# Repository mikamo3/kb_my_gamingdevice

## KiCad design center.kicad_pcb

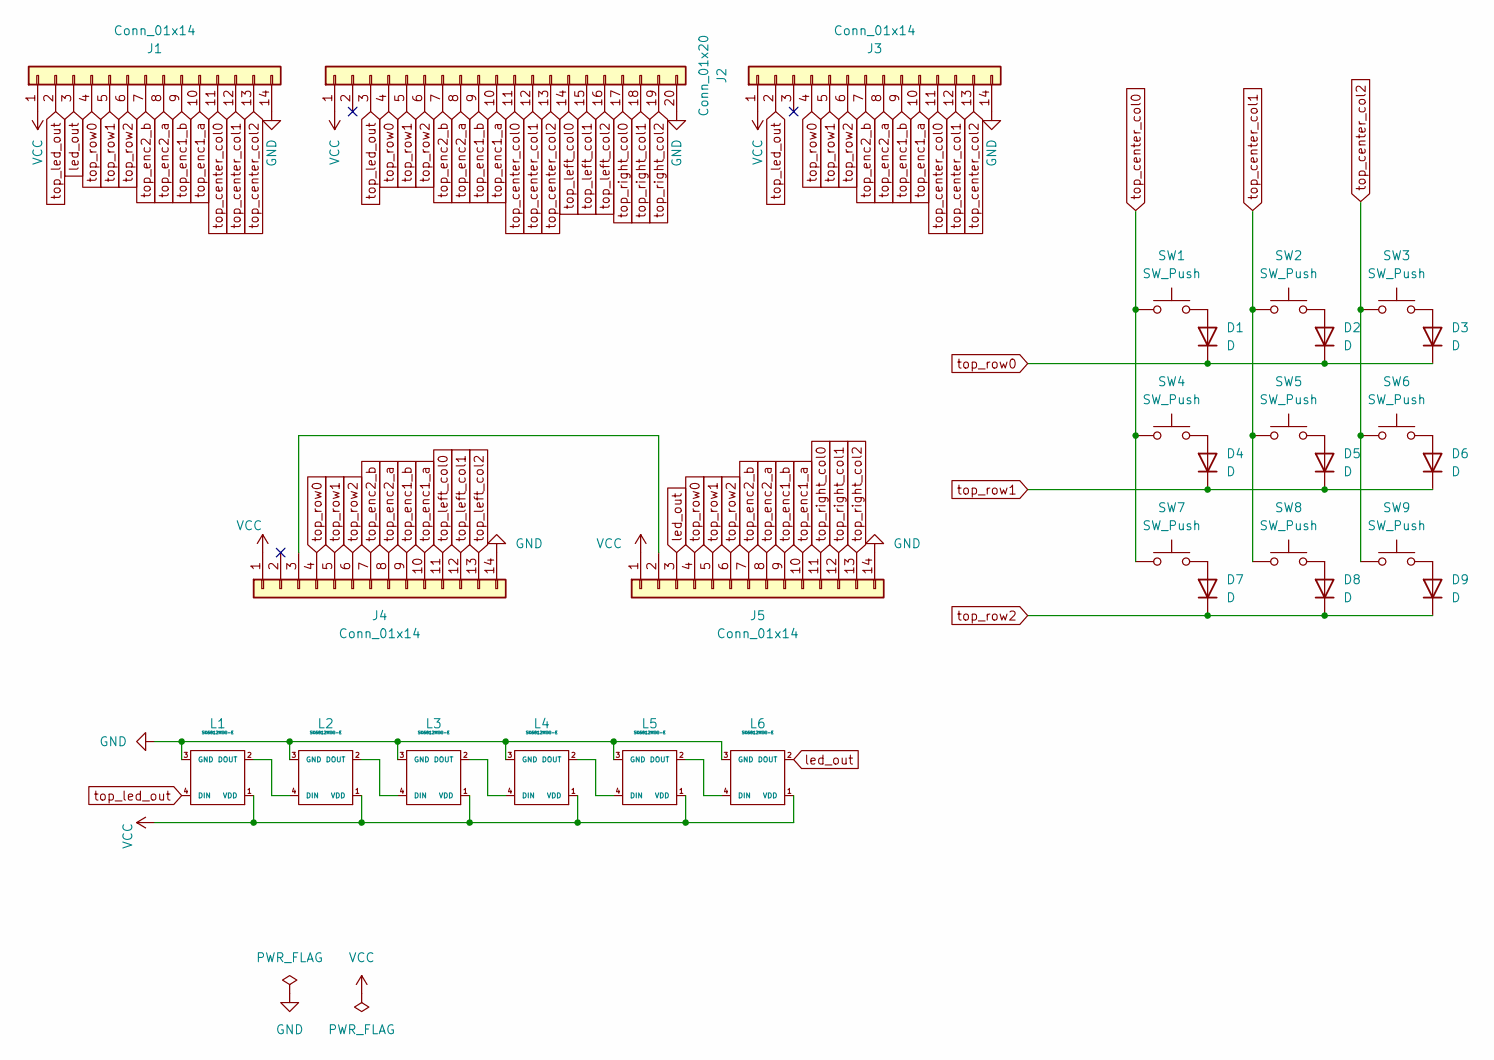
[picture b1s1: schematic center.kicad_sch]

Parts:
D1, D2, D3, D4, D5, D6, D7, D8, D9: D; D_SOD-123
J1, J3: Conn_01x14; PinSocket_2x07_P2.54mm_Horizontal
J2: Conn_01x20; PinSocket_2x10_P2.54mm_Horizontal
J4, J5: Conn_01x14; PinHeader_2x07_P2.54mm_Horizontal
L1, L2, L3, L4, L5, L6: SK6812MINI-E; YS-SK6812MINI-E
SW1, SW2, SW3, SW4, SW5, SW6, SW7, SW8, SW9: SW_Push; CherryMX_Hotswap_1u

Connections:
GND: J1.14, J2.20, J3.14, J4.14, J5.14, L1.3 (GND), L2.3 (GND), L3.3 (GND), L4.3 (GND), L5.3 (GND), L6.3 (GND)
unnamed: D1.2 (A), SW1.2
unnamed: D2.2 (A), SW2.2
unnamed: D3.2 (A), SW3.2
unnamed: D4.2 (A), SW4.2
unnamed: D5.2 (A), SW5.2
unnamed: D6.2 (A), SW6.2
unnamed: D7.2 (A), SW7.2
unnamed: D8.2 (A), SW8.2
unnamed: D9.2 (A), SW9.2
unnamed: J4.3, J5.2
unnamed: L1.2 (DOUT), L2.4 (DIN)
unnamed: L2.2 (DOUT), L3.4 (DIN)
unnamed: L3.2 (DOUT), L4.4 (DIN)
unnamed: L4.2 (DOUT), L5.4 (DIN)
unnamed: L5.2 (DOUT), L6.4 (DIN)
VCC: J1.1, J2.1, J3.1, J4.1, J5.1, L1.1 (VDD), L2.1 (VDD), L3.1 (VDD), L4.1 (VDD), L5.1 (VDD), L6.1 (VDD)
led_out: J1.3, J5.3, L6.2 (DOUT)
top_center_col0: J1.11, J2.11, J3.11, SW1.1, SW4.1, SW7.1
top_center_col1: J1.12, J2.12, J3.12, SW2.1, SW5.1, SW8.1
top_center_col2: J1.13, J2.13, J3.13, SW3.1, SW6.1, SW9.1
top_enc1_a: J1.10, J2.10, J3.10, J4.10, J5.10
top_enc1_b: J1.9, J2.9, J3.9, J4.9, J5.9
top_enc2_a: J1.8, J2.8, J3.8, J4.8, J5.8
top_enc2_b: J1.7, J2.7, J3.7, J4.7, J5.7
top_led_out: J1.2, J2.3, J3.2, L1.4 (DIN)
top_left_col0: J2.14, J4.11
top_left_col1: J2.15, J4.12
top_left_col2: J2.16, J4.13
top_right_col0: J2.17, J5.11
top_right_col1: J2.18, J5.12
top_right_col2: J2.19, J5.13
top_row0: D1.1 (K), D2.1 (K), D3.1 (K), J1.4, J2.4, J3.4, J4.4, J5.4
top_row1: D4.1 (K), D5.1 (K), D6.1 (K), J1.5, J2.5, J3.5, J4.5, J5.5
top_row2: D7.1 (K), D8.1 (K), D9.1 (K), J1.6, J2.6, J3.6, J4.6, J5.6

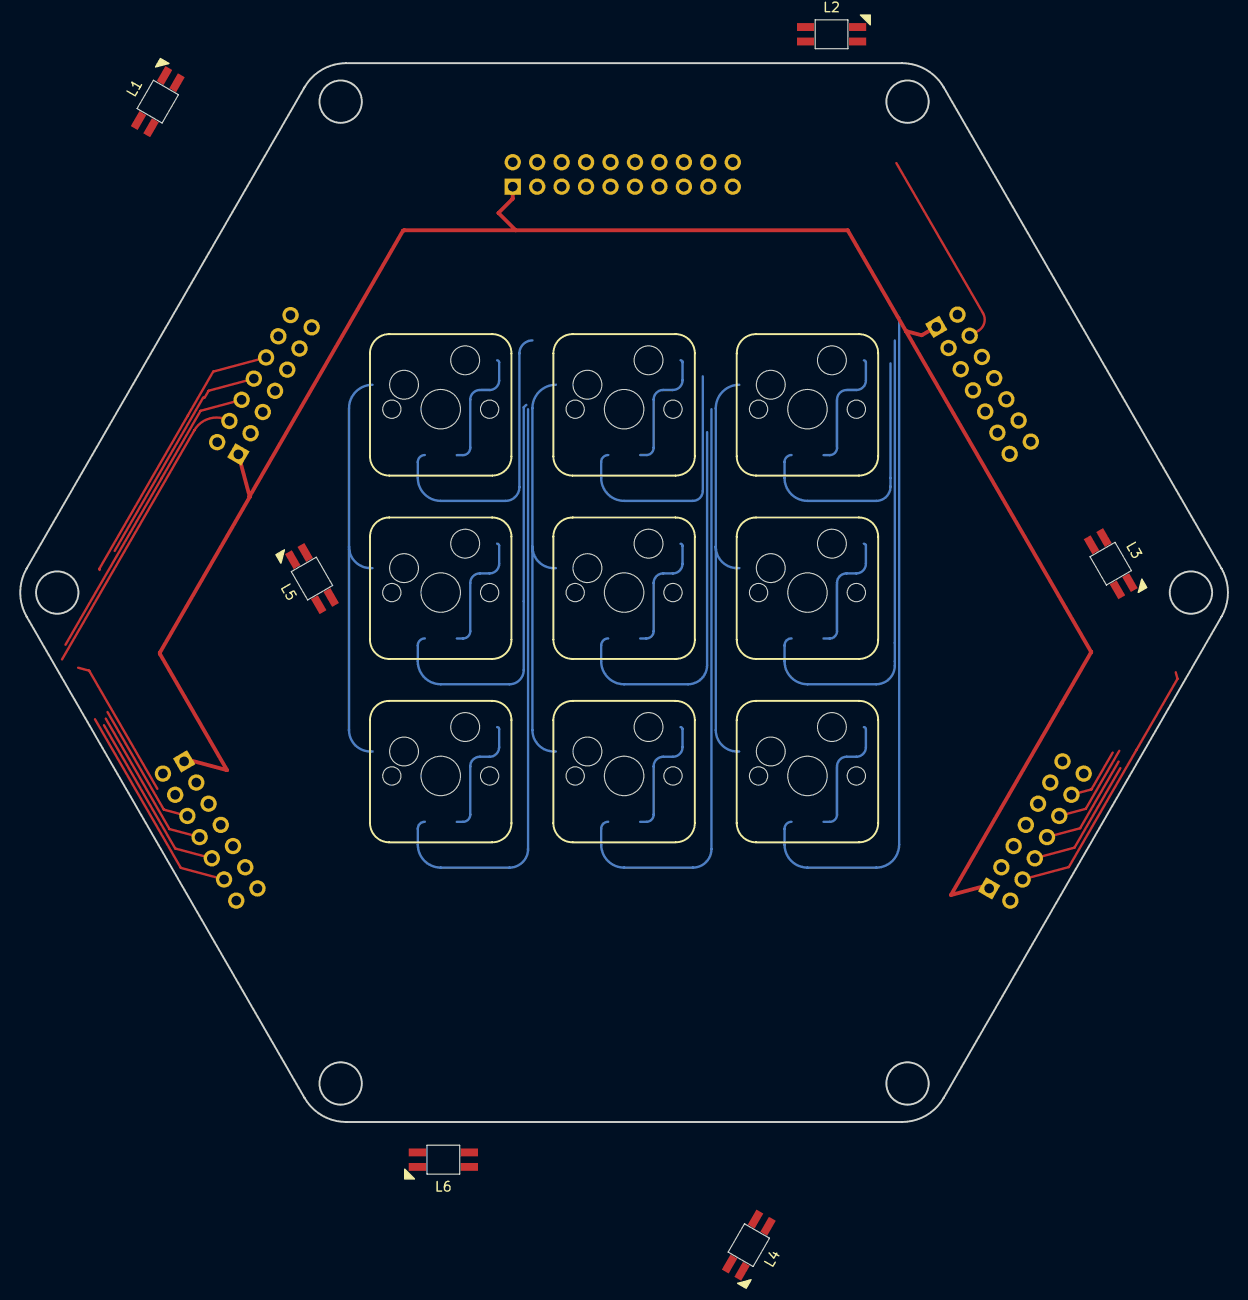
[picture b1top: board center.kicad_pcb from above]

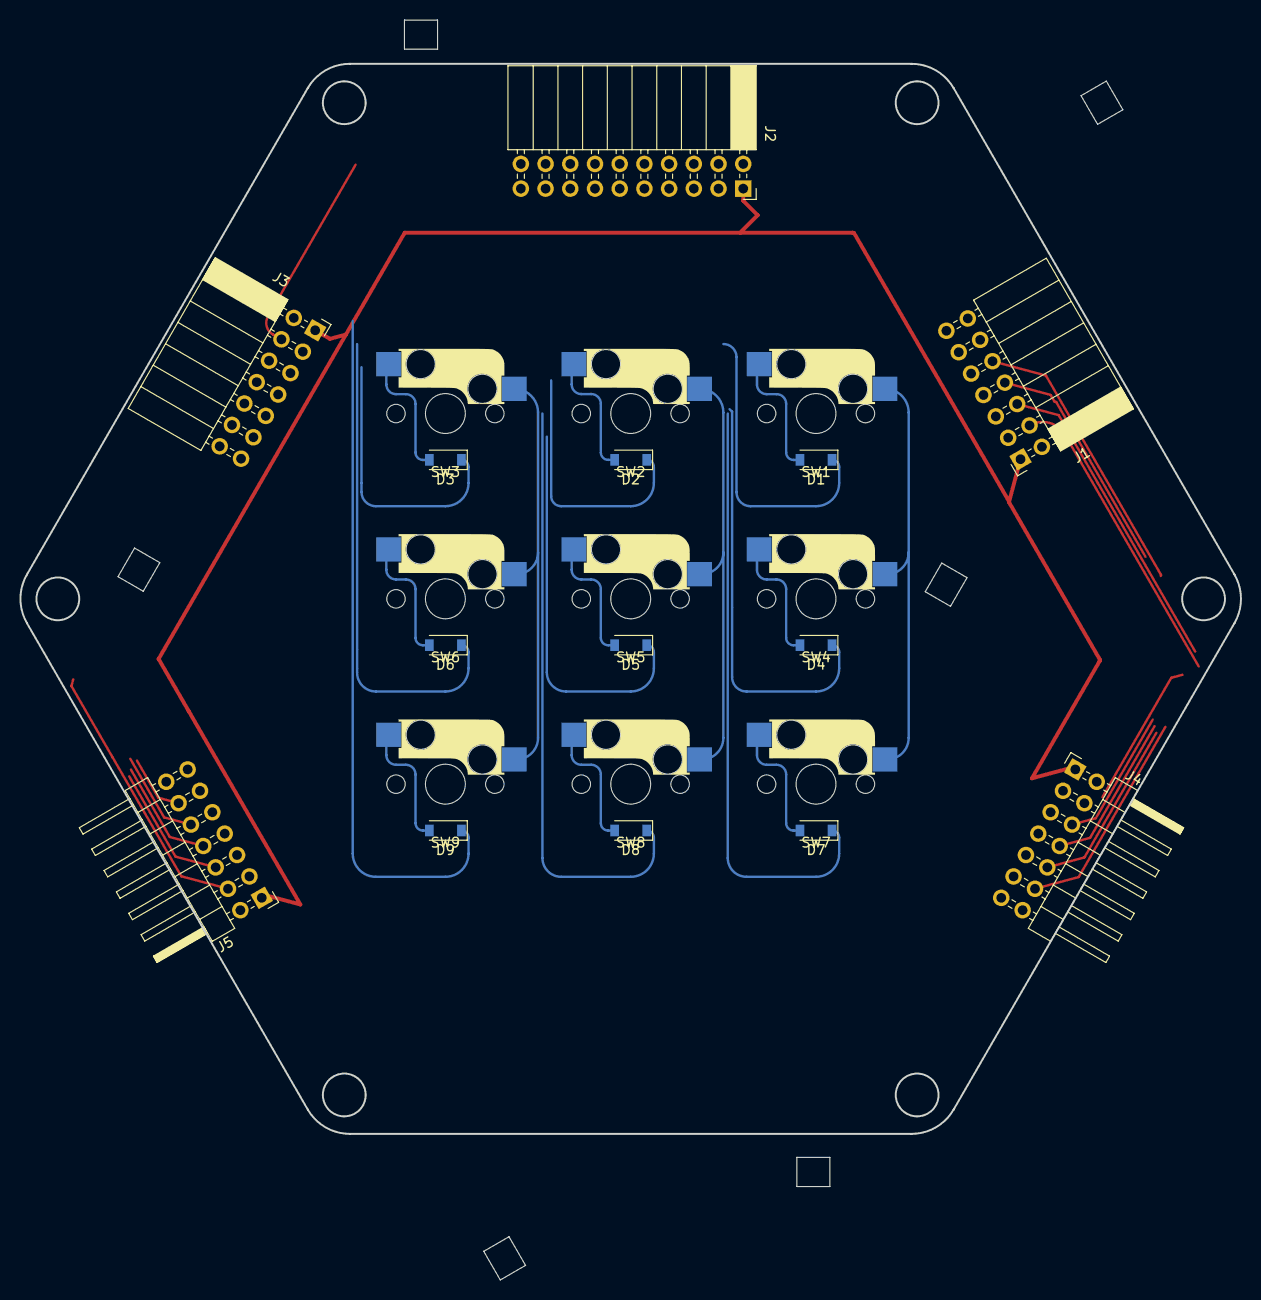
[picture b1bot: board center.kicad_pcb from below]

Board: 2 copper layers, 125.5 x 129.4 mm, 29 parts (14 on the bottom side), 35 nets.

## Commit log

2023-06-17 :sparkles: (add) all
